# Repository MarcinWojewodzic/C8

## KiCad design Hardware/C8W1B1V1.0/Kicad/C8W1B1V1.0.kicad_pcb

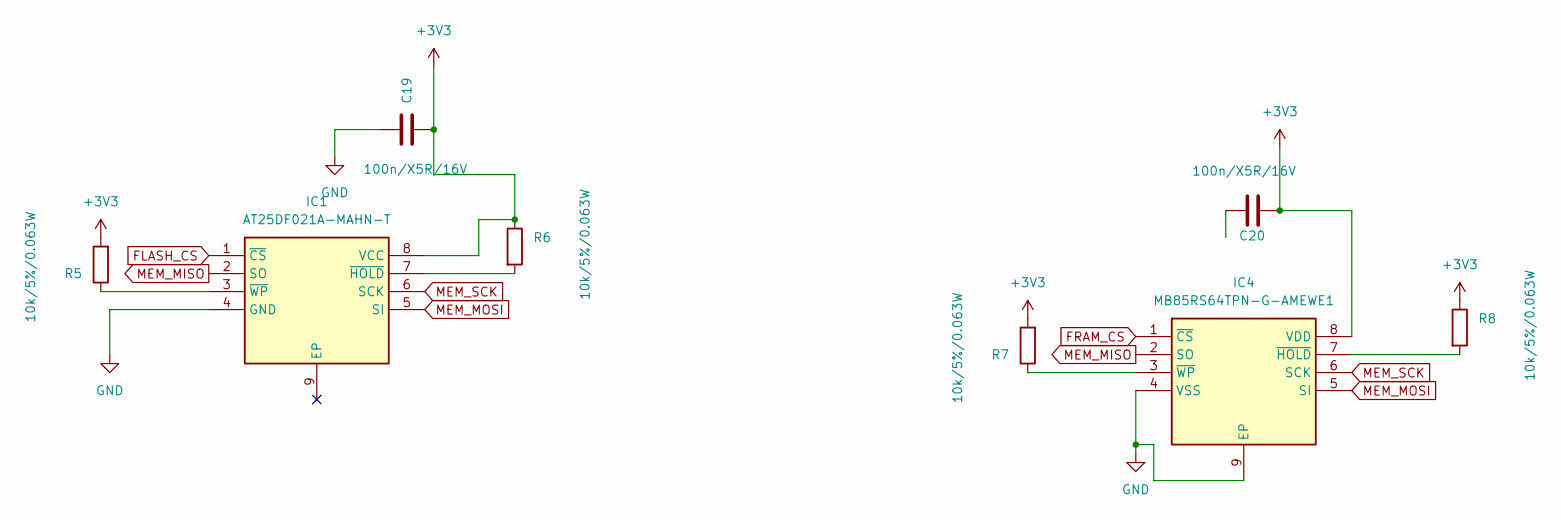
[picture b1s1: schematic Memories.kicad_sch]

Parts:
C19, C20: 100n/X5R/16V; C_0402_1005Metric
IC1: AT25DF021A-MAHN-T; SON50P300X200X60-9N; Manufacturer_Part_Number AT25DF021A-MAHN-T
IC4: MB85RS64TPN-G-AMEWE1; SON50P300X200X75-9N; Manufacturer_Part_Number MB85RS64TPN-G-AMEWE1; Mouser Part Number N/A
R5, R6, R7, R8: 10k/5%/0.063W; R_0402_1005Metric

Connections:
+3V3: C19.2, C20.1, IC1.8 (VCC), IC4.8 (VDD), R5.2, R6.1, R7.2, R8.1; also elsewhere on the board
FLASH_CS: IC1.1 (~CS); also elsewhere on the board
FRAM_CS: IC4.1 (~CS); also elsewhere on the board
GND: C19.1, IC1.4 (GND), IC4.4 (VSS), IC4.9 (EP); also elsewhere on the board
MEM_MISO: IC1.2 (SO), IC4.2 (SO); also elsewhere on the board
MEM_MOSI: IC1.5 (SI), IC4.5 (SI); also elsewhere on the board
MEM_SCK: IC1.6 (SCK), IC4.6 (SCK); also elsewhere on the board
unnamed: IC1.7 (~HOLD), R6.2
unnamed: IC1.3 (~WP), R5.1
unnamed: IC4.7 (~HOLD), R8.2
unnamed: IC4.3 (~WP), R7.1

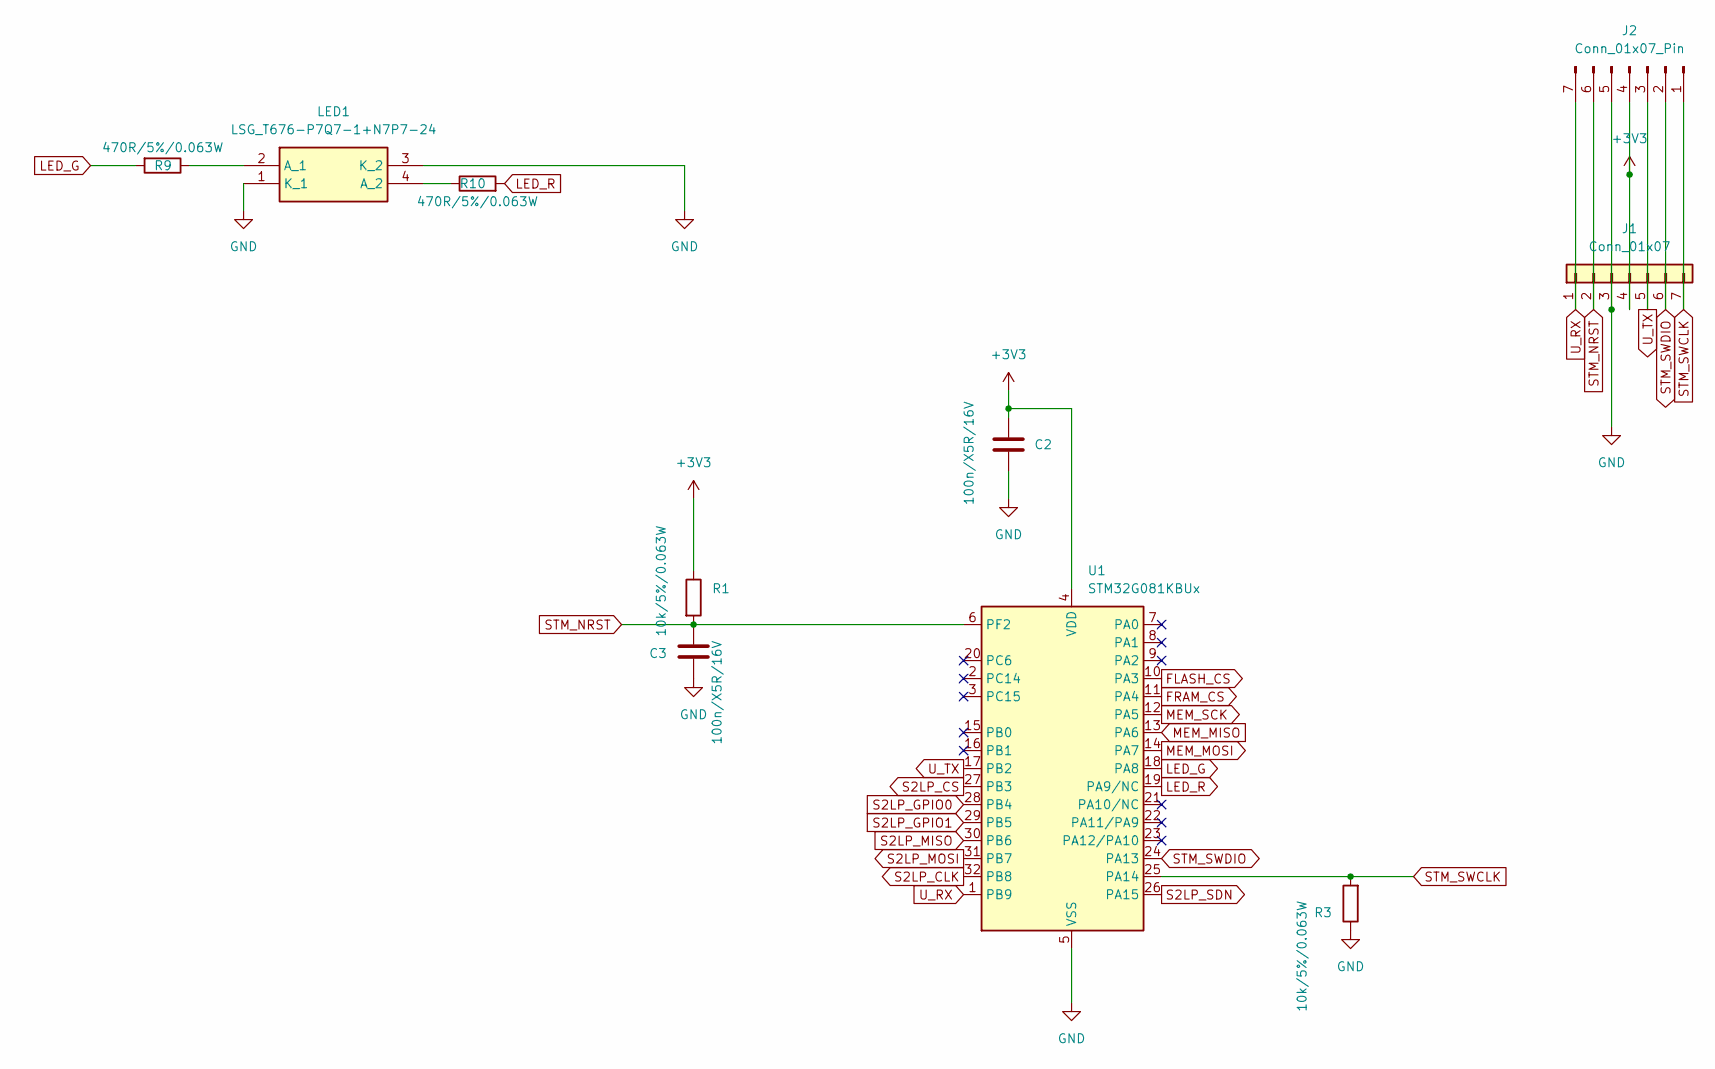
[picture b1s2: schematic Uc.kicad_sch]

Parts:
C2, C3: 100n/X5R/16V; C_0402_1005Metric
J1: Conn_01x07; PinHeader_1x07_P2.54mm_Vertical
J2: Conn_01x07_Pin; Conn_1x7_SMD
LED1: LSG_T676-P7Q7-1+N7P7-24; LSGT676P7Q71N7P724; Manufacturer_Part_Number LSG T676-P7Q7-1+N7P7-24; Mouser Part Number 720-LSGT676P7Q71N7P7
R1, R3: 10k/5%/0.063W; R_0402_1005Metric
R9, R10: 470R/5%/0.063W; R_0402_1005Metric
U1: STM32G081KBUx; QFN-32-1EP_5x5mm_P0.5mm_EP3.45x3.45mm

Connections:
+3V3: C2.1, J1.4, J2.4, R1.1, U1.4 (VDD); also elsewhere on the board
FLASH_CS: U1.10 (PA3); also elsewhere on the board
FRAM_CS: U1.11 (PA4); also elsewhere on the board
GND: C2.2, C3.2, J1.3, J2.5, LED1.1 (K_1), LED1.3 (K_2), R3.1, U1.5 (VSS), U1.33 (VSS); also elsewhere on the board
LED_G: R9.2, U1.18 (PA8)
LED_R: R10.2, U1.19 (PA9/NC)
MEM_MISO: U1.13 (PA6); also elsewhere on the board
MEM_MOSI: U1.14 (PA7); also elsewhere on the board
MEM_SCK: U1.12 (PA5); also elsewhere on the board
unnamed: LED1.2 (A_1), R9.1
unnamed: LED1.4 (A_2), R10.1
S2LP_CLK: U1.32 (PB8); also elsewhere on the board
S2LP_CS: U1.27 (PB3); also elsewhere on the board
S2LP_GPIO0: U1.28 (PB4); also elsewhere on the board
S2LP_GPIO1: U1.29 (PB5); also elsewhere on the board
S2LP_MISO: U1.30 (PB6); also elsewhere on the board
S2LP_MOSI: U1.31 (PB7); also elsewhere on the board
S2LP_SDN: U1.26 (PA15); also elsewhere on the board
STM_NRST: C3.1, J1.2, J2.6, R1.2, U1.6 (PF2)
STM_SWCLK: J1.7, J2.1, R3.2, U1.25 (PA14)
STM_SWDIO: J1.6, J2.2, U1.24 (PA13)
U_RX: J1.1, J2.7, U1.1 (PB9)
U_TX: J1.5, J2.3, U1.17 (PB2)

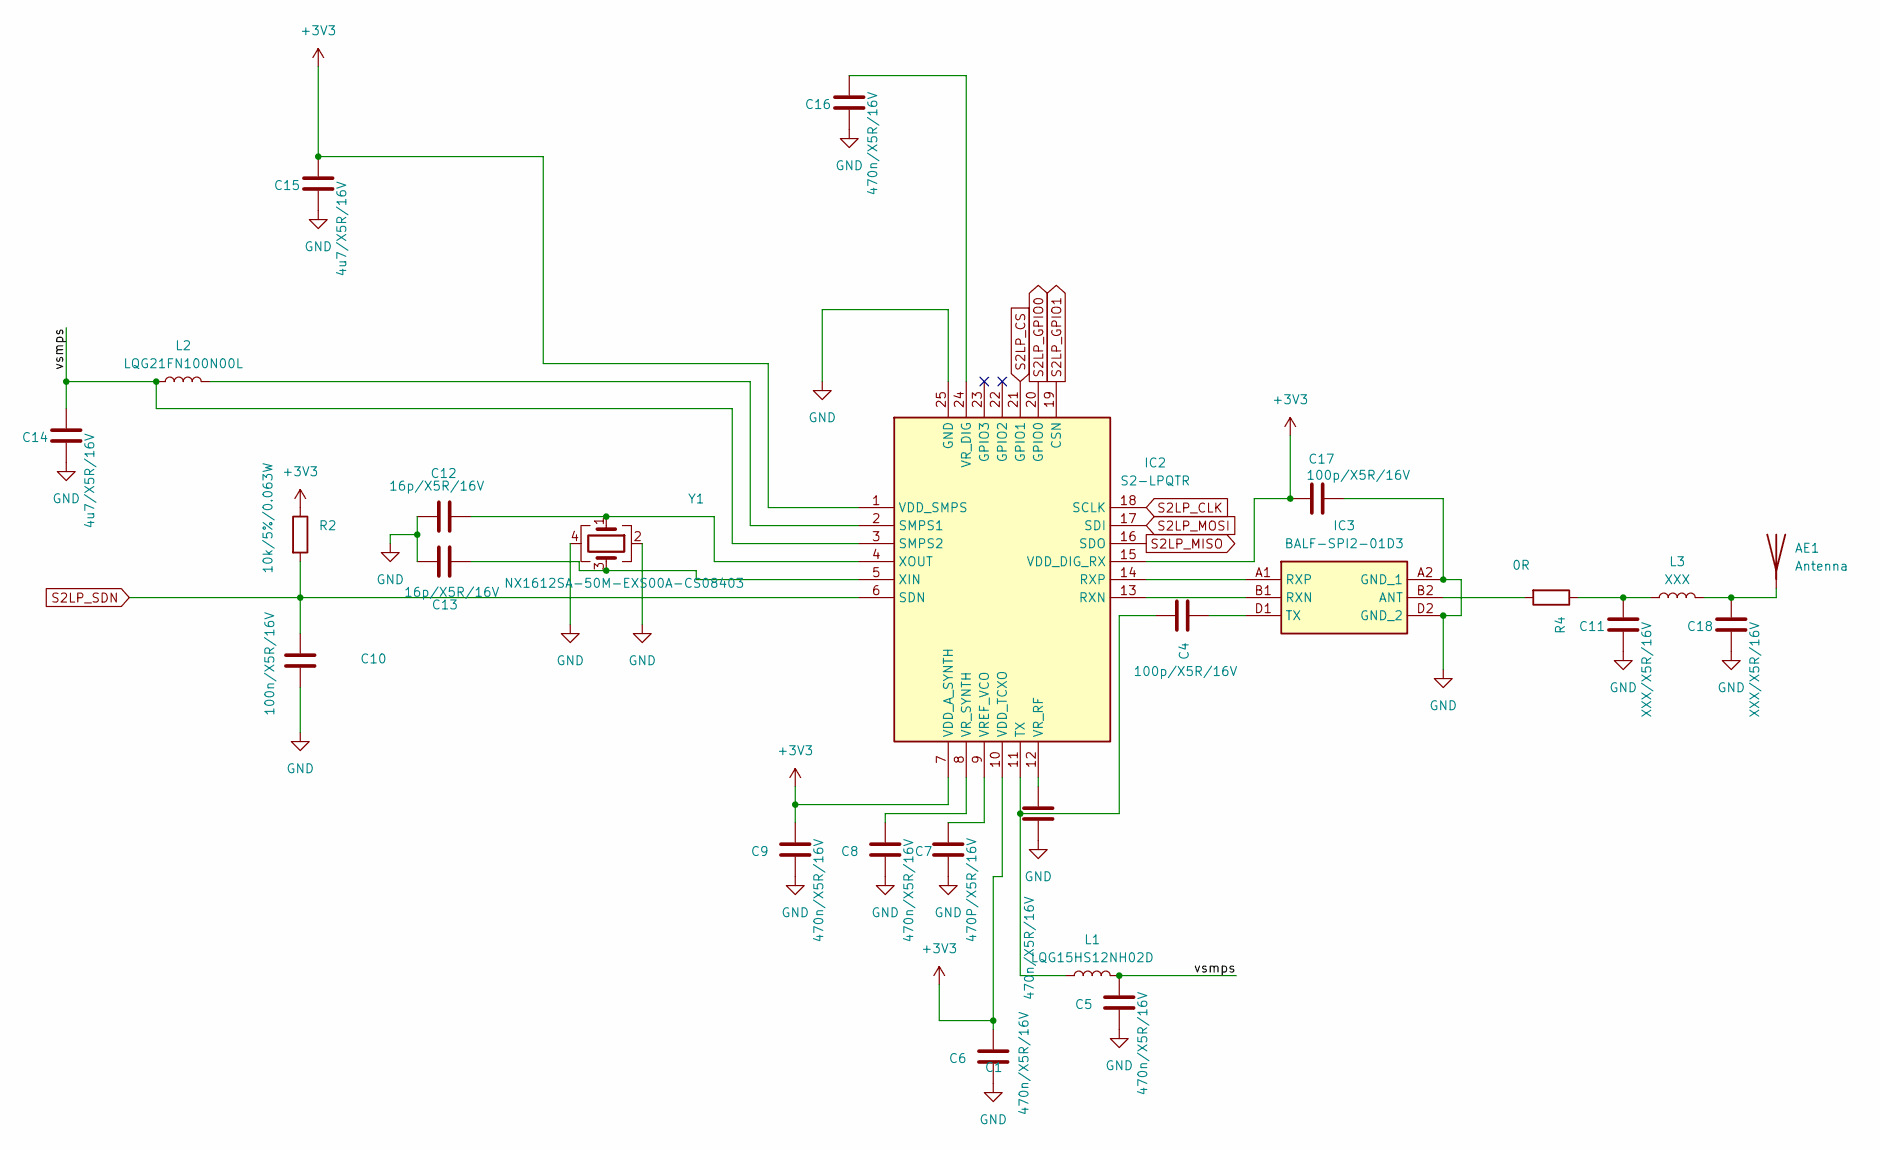
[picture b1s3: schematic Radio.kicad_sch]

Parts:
AE1: Antenna; Texas_SWRA416_868MHz_915MHz
C1, C5, C6, C8, C9, C16: 470n/X5R/16V; C_0402_1005Metric
C4, C17: 100p/X5R/16V; C_0402_1005Metric
C7: 470P/X5R/16V; C_0402_1005Metric
C10: 100n/X5R/16V; C_0402_1005Metric
C11, C18: XXX/X5R/16V; C_0402_1005Metric
C12, C13: 16p/X5R/16V; C_0402_1005Metric
C14, C15: 4u7/X5R/16V; C_0402_1005Metric
IC2: S2-LPQTR; QFN50P400X400X100-25N-D; Manufacturer_Part_Number S2-LPQTR; Mouser Part Number 511-S2-LPQTR
IC3: BALF-SPI2-01D3; BALFSPI201D3; Manufacturer_Part_Number BALF-SPI2-01D3; Mouser Part Number 511-BALF-SPI2-01D3
L1: LQG15HS12NH02D; L_0402_1005Metric
L2: LQG21FN100N00L; L_0805_2012Metric
L3: XXX; L_0402_1005Metric
R2: 10k/5%/0.063W; R_0402_1005Metric
R4: 0R; R_0402_1005Metric
Y1: NX1612SA-50M-EXS00A-CS08403; Oscillator_SMD_Abracon_ASCO-4Pin_1.6x1.2mm

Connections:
+3V3: C6.1, C9.1, C15.1, C17.1, IC2.1 (VDD_SMPS), IC2.7 (VDD_A_SYNTH), IC2.10 (VDD_TCXO), IC2.15 (VDD_DIG_RX), R2.1; also elsewhere on the board
/Radio/vsmps: C5.1, C14.1, IC2.3 (SMPS2), L1.2, L2.1
GND: C1.2, C5.2, C6.2, C7.2, C8.2, C9.2, C10.2, C11.2, C12.2, C13.1, C14.2, C15.2, C16.2, C17.2, C18.2, IC2.25 (GND), IC3.A2 (GND_1), IC3.D2 (GND_2), Y1.2, Y1.4; also elsewhere on the board
unnamed: AE1.1 (A), C18.1, L3.2
unnamed: C11.1, L3.1, R4.1
unnamed: IC2.13 (RXN), IC3.B1 (RXN)
unnamed: IC2.14 (RXP), IC3.A1 (RXP)
unnamed: IC2.2 (SMPS1), L2.2
unnamed: C4.1, IC2.11 (TX), L1.1
unnamed: C7.1, IC2.9 (VREF_VCO)
unnamed: C16.1, IC2.24 (VR_DIG)
unnamed: C1.1, IC2.12 (VR_RF)
unnamed: C8.1, IC2.8 (VR_SYNTH)
unnamed: C13.2, IC2.5 (XIN), Y1.3
unnamed: C12.1, IC2.4 (XOUT), Y1.1
unnamed: IC3.B2 (ANT), R4.2
unnamed: C4.2, IC3.D1 (TX)
S2LP_CLK: IC2.18 (SCLK); also elsewhere on the board
S2LP_CS: IC2.21 (GPIO1); also elsewhere on the board
S2LP_GPIO0: IC2.20 (GPIO0); also elsewhere on the board
S2LP_GPIO1: IC2.19 (CSN); also elsewhere on the board
S2LP_MISO: IC2.16 (SDO); also elsewhere on the board
S2LP_MOSI: IC2.17 (SDI); also elsewhere on the board
S2LP_SDN: C10.1, IC2.6 (SDN), R2.2; also elsewhere on the board

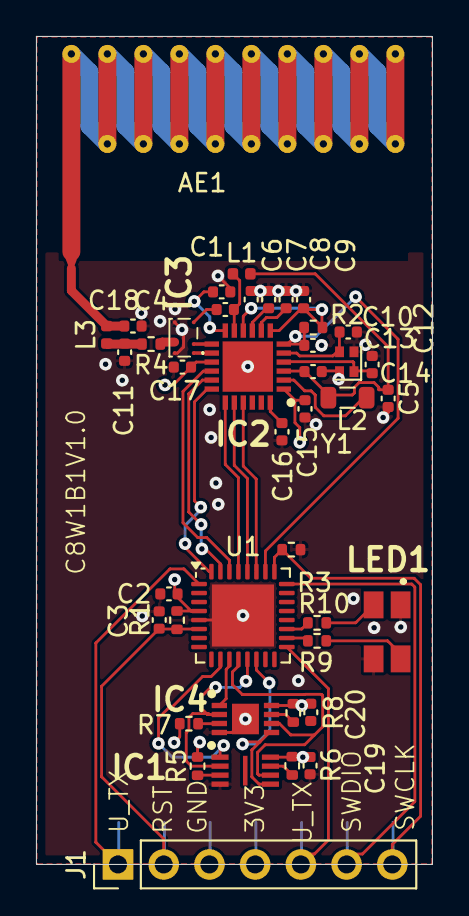
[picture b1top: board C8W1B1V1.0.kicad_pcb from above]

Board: 4 copper layers, 22.0 x 46.0 mm, 43 parts (1 on the bottom side), 42 nets.

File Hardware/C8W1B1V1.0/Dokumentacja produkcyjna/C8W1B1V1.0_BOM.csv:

"Id";"Oznaczenie";"Footprint";"Liczba";"Oznaczenie";"Dostawca i numer artykułu";
1;"C12,C13";"C_0402_1005Metric";2;"16p/X5R/16V";;;
2;"C3,C20,C2,C19,C10";"C_0402_1005Metric";5;"100n/X5R/16V";;;
3;"R9,R10";"R_0402_1005Metric";2;"470R/5%/0.063W";;;
4;"Y1";"Oscillator_SMD_Abracon_ASCO-4Pin_1.6x1.2mm";1;"NX1612SA-50M-EXS00A-CS08403";;;
5;"R4";"R_0402_1005Metric";1;"0R";;;
6;"LED1";"LSGT676P7Q71N7P724";1;"LSG_T676-P7Q7-1+N7P7-24";;;
7;"R5,R1,R3,R6,R8,R2,R7";"R_0402_1005Metric";7;"10k/5%/0.063W";;;
8;"C1,C6,C8,C9,C16,C5";"C_0402_1005Metric";6;"470n/X5R/16V";;;
9;"C7";"C_0402_1005Metric";1;"470P/X5R/16V";;;
10;"J1";"PinHeader_1x07_P2.54mm_Vertical";1;"Conn_01x07";;;
11;"IC3";"BALFSPI201D3";1;"BALF-SPI2-01D3";;;
12;"L3";"L_0402_1005Metric";1;"XXX";;;
13;"C14,C15";"C_0402_1005Metric";2;"4u7/X5R/16V";;;
14;"IC1";"SON50P300X200X60-9N";1;"AT25DF021A-MAHN-T";;;
15;"IC4";"SON50P300X200X75-9N";1;"MB85RS64TPN-G-AMEWE1";;;
16;"C4,C17";"C_0402_1005Metric";2;"100p/X5R/16V";;;
17;"C18,C11";"C_0402_1005Metric";2;"XXX/X5R/16V";;;
18;"AE1";"Texas_SWRA416_868MHz_915MHz";1;"Antenna";;;
19;"L1";"L_0402_1005Metric";1;"LQG15HS12NJD2D";;;
20;"U1";"QFN-32-1EP_5x5mm_P0.5mm_EP3.45x3.45mm";1;"STM32G081KBUx";;;
21;"L2";"L_0805_2012Metric";1;"LQG21FN100N00L";;;
22;"IC2";"QFN50P400X400X100-25N-D";1;"S2-LPQTR";;;
23;"J2";"Conn_1x7_SMD";1;"Conn_01x07_Pin";;;

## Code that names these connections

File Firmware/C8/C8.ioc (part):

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Mcu.Name=STM32G081KBUx
Mcu.Package=UFQFPN32
Mcu.UserName=STM32G081KBUx
PA13.Mode=Serial_Wire
PA13.Signal=SYS_SWDIO
PA14-BOOT0.Mode=Serial_Wire
PA14-BOOT0.Signal=SYS_SWCLK
PA15.GPIOParameters=GPIO_Speed,GPIO_Label
PA15.GPIO_Label=S2LP_SDN
PA15.GPIO_Speed=GPIO_SPEED_FREQ_VERY_HIGH
PA15.Signal=GPIO_Output
PA3.GPIOParameters=GPIO_Speed,PinState,GPIO_Label
PA3.GPIO_Label=FLASH_CS
PA3.GPIO_Speed=GPIO_SPEED_FREQ_VERY_HIGH
PA3.PinState=GPIO_PIN_SET
PA3.Signal=GPIO_Output
PA4.GPIOParameters=GPIO_Speed,PinState,GPIO_Label
PA4.GPIO_Label=FRAM_CS
PA4.GPIO_Speed=GPIO_SPEED_FREQ_VERY_HIGH
PA4.PinState=GPIO_PIN_SET
PA4.Signal=GPIO_Output
PA5.Mode=Full_Duplex_Master
PA5.Signal=SPI1_SCK
PA6.Mode=Full_Duplex_Master
PA6.Signal=SPI1_MISO
PA7.Mode=Full_Duplex_Master
PA7.Signal=SPI1_MOSI
PA8.Signal=S_TIM1_CH1
PA9.Signal=S_TIM1_CH2
PB0.GPIOParameters=GPIO_Speed,GPIO_Label
PB0.GPIO_Label=FRAM_CS
PB0.GPIO_Speed=GPIO_SPEED_FREQ_VERY_HIGH
PB0.Signal=GPIO_Output
PB1.GPIOParameters=GPIO_Speed,GPIO_Label
PB1.GPIO_Label=FLASH_CS
PB1.GPIO_Speed=GPIO_SPEED_FREQ_VERY_HIGH
PB1.Signal=GPIO_Output
PB2.Mode=Asynchronous
PB2.Signal=USART3_TX
PB3.GPIOParameters=GPIO_Speed,GPIO_Label
PB3.GPIO_Label=S2LP_CS
PB3.GPIO_Speed=GPIO_SPEED_FREQ_VERY_HIGH
PB3.Signal=GPIO_Output
PB4.GPIOParameters=GPIO_Label
PB4.GPIO_Label=S2LP_GPIO0
PB4.Signal=GPXTI4
PB5.GPIOParameters=GPIO_Label
PB5.GPIO_Label=S2LP_GPIO1
PB5.Signal=GPXTI5
PB6.Mode=Full_Duplex_Master
PB6.Signal=SPI2_MISO
PB7.Mode=Full_Duplex_Master
PB7.Signal=SPI2_MOSI
PB8.Mode=Full_Duplex_Master
PB8.Signal=SPI2_SCK
PB9.Mode=Asynchronous
PB9.Signal=USART3_RX
RCC.HSE_VALUE=8000000
RCC.SYSCLKFreq_VALUE=64000000
RCC.SYSCLKSource=RCC_SYSCLKSOURCE_PLLCLK
board=custom

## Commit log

2024-11-08 Initial commit// Skończono PCB
2024-11-16 Dodano nazwę na PCB
